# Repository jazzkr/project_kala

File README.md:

View this project on [CADLAB.io](https://cadlab.io/project/22756). 

# project_kala

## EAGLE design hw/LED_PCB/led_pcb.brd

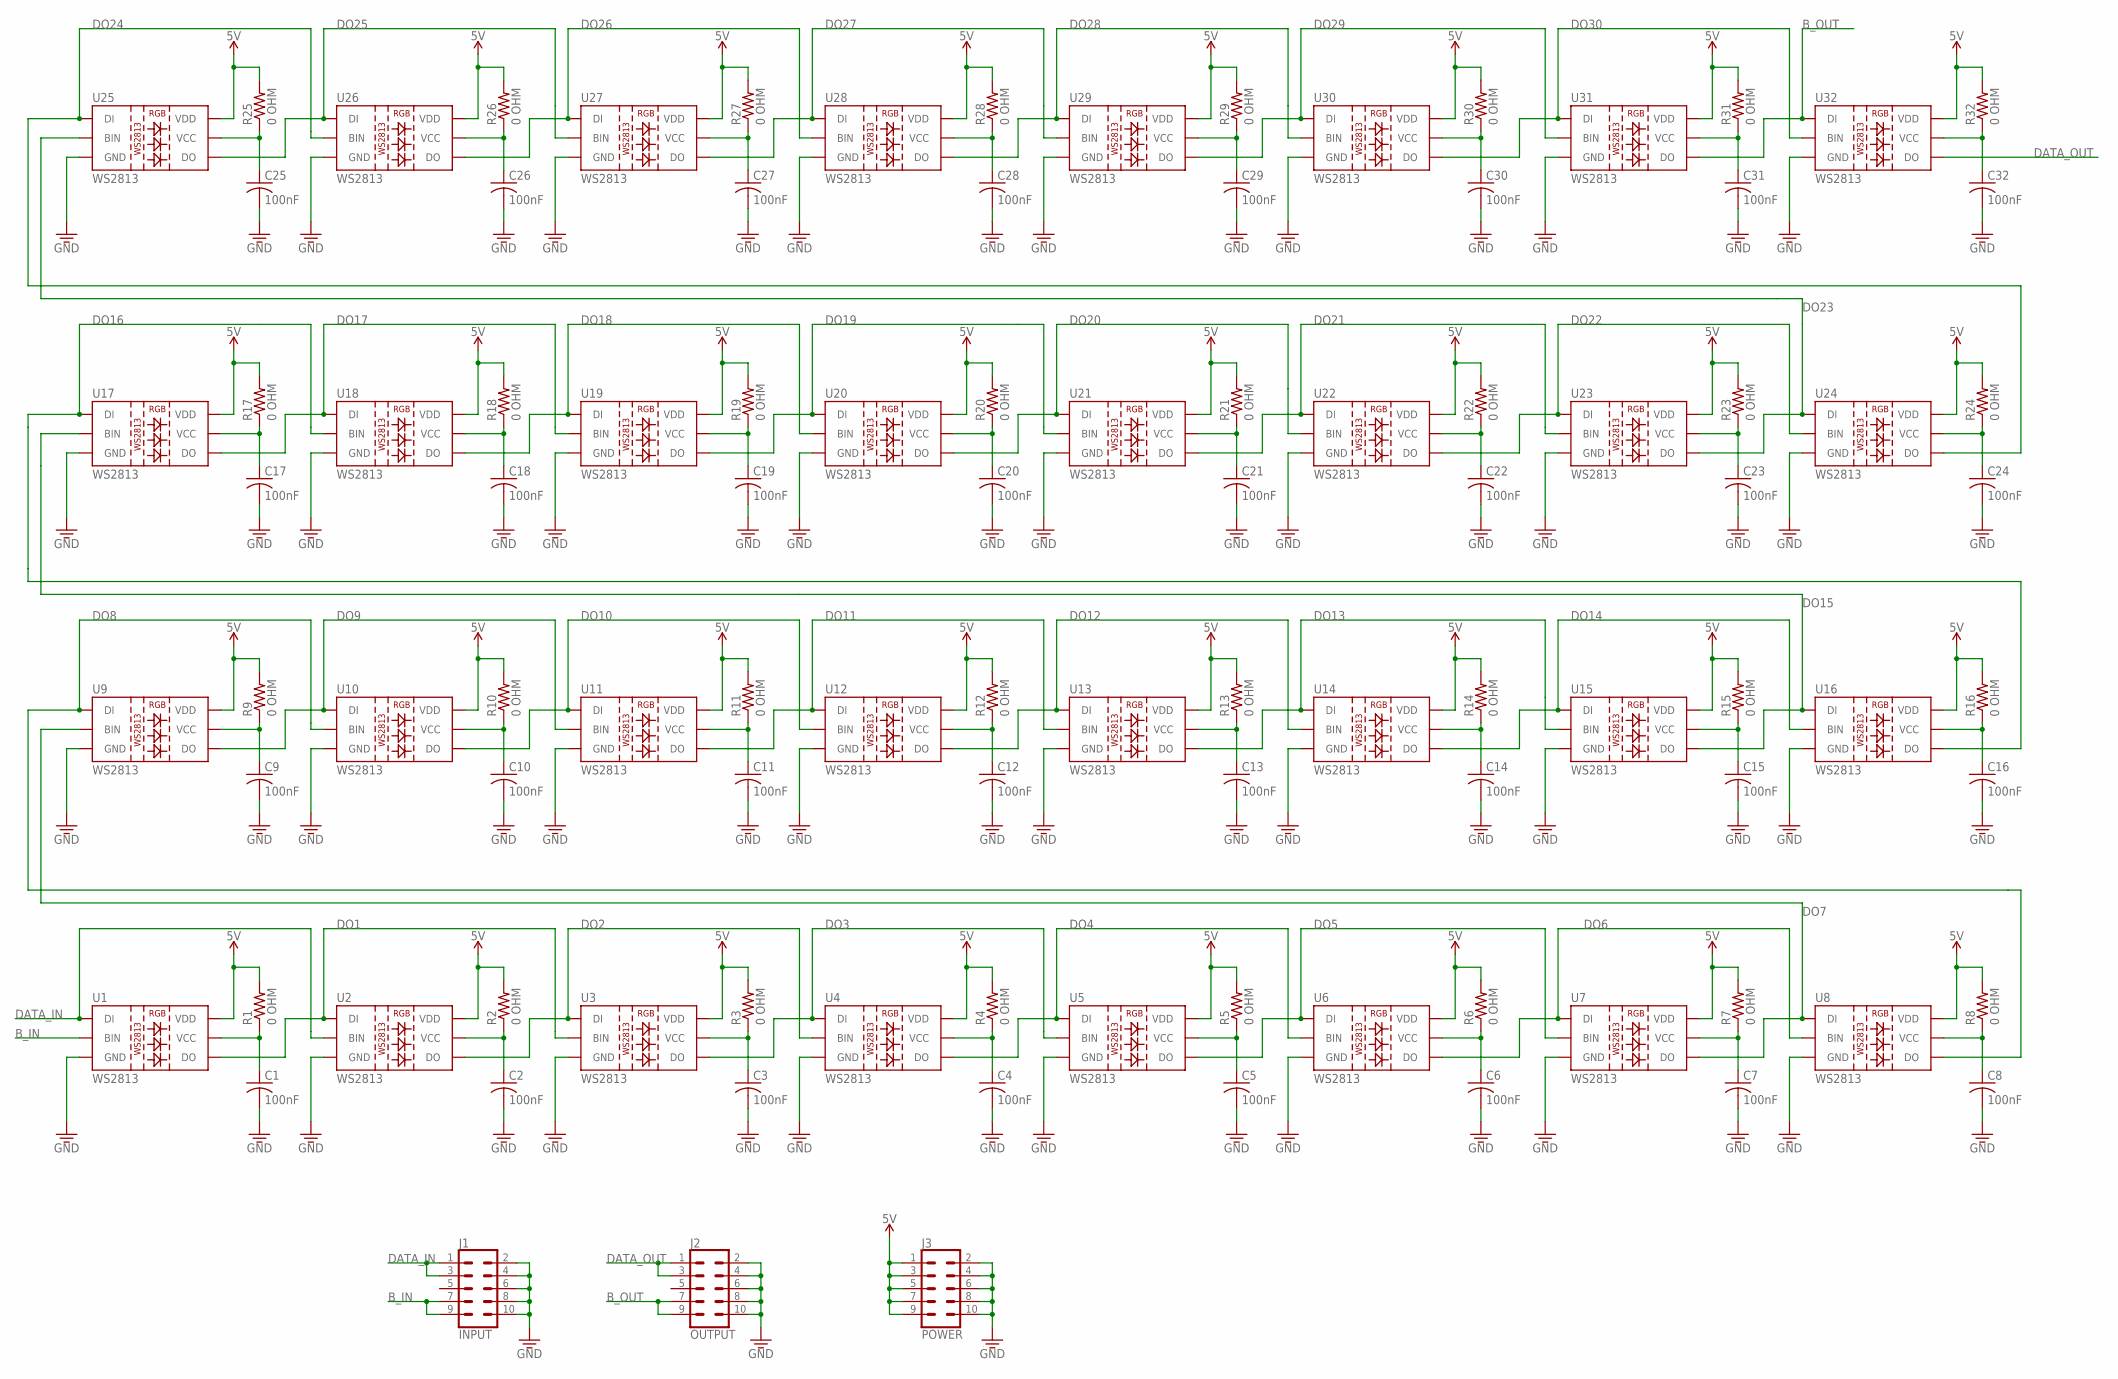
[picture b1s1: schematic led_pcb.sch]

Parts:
C1, C2, C3, C4, C5, C6, C7, C8, C9, C10, C11, C12, C13, C14, C15, C16, C17, C18, C19, C20, C21, C22, C23, C24, C25, C26, C27, C28, C29, C30, C31, C32: 100nF; C0805K
J1: INPUT; 2X5-SHROUDED_SMD
J2: OUTPUT; 2X5-SHROUDED_SMD
J3: POWER; 2X5-SHROUDED_SMD
R1, R2, R3, R4, R5, R6, R7, R8, R9, R10, R11, R12, R13, R14, R15, R16, R17, R18, R19, R20, R21, R22, R23, R24, R25, R26, R27, R28, R29, R30, R31, R32: 0 OHM; M0805
U1, U2, U3, U4, U5, U6, U7, U8, U9, U10, U11, U12, U13, U14, U15, U16, U17, U18, U19, U20, U21, U22, U23, U24, U25, U26, U27, U28, U29, U30, U31, U32: WS2813

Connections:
5V: J3.1, J3.3, J3.5, J3.7, J3.9, R1.2, R2.2, R3.2, R4.2, R5.2, R6.2, R7.2, R8.2, R9.2, R10.2, R11.2, R12.2, R13.2, R14.2, R15.2, R16.2, R17.2, R18.2, R19.2, R20.2, R21.2, R22.2, R23.2, R24.2, R25.2, R26.2, R27.2, R28.2, R29.2, R30.2, R31.2, R32.2, U1.2 (VDD), U2.2 (VDD), U3.2 (VDD), U4.2 (VDD), U5.2 (VDD), U6.2 (VDD), U7.2 (VDD), U8.2 (VDD), U9.2 (VDD), U10.2 (VDD), U11.2 (VDD), U12.2 (VDD), U13.2 (VDD), U14.2 (VDD), U15.2 (VDD), U16.2 (VDD), U17.2 (VDD), U18.2 (VDD), U19.2 (VDD), U20.2 (VDD), U21.2 (VDD), U22.2 (VDD), U23.2 (VDD), U24.2 (VDD), U25.2 (VDD), U26.2 (VDD), U27.2 (VDD), U28.2 (VDD), U29.2 (VDD), U30.2 (VDD), U31.2 (VDD), U32.2 (VDD)
B_IN: J1.7, J1.9, U1.6 (BIN)
B_OUT: J2.7, J2.9, U31.3 (DO), U32.4 (DI)
DATA_IN: J1.1, J1.3, U1.4 (DI), U2.6 (BIN)
DATA_OUT: J2.1, J2.3, U32.3 (DO)
DO1: U1.3 (DO), U2.4 (DI), U3.6 (BIN)
DO2: U2.3 (DO), U3.4 (DI), U4.6 (BIN)
DO3: U3.3 (DO), U4.4 (DI), U5.6 (BIN)
DO4: U4.3 (DO), U5.4 (DI), U6.6 (BIN)
DO5: U5.3 (DO), U6.4 (DI), U7.6 (BIN)
DO6: U6.3 (DO), U7.4 (DI), U8.6 (BIN)
DO7: U7.3 (DO), U8.4 (DI), U9.6 (BIN)
DO8: U8.3 (DO), U9.4 (DI), U10.6 (BIN)
DO9: U9.3 (DO), U10.4 (DI), U11.6 (BIN)
DO10: U10.3 (DO), U11.4 (DI), U12.6 (BIN)
DO11: U11.3 (DO), U12.4 (DI), U13.6 (BIN)
DO12: U12.3 (DO), U13.4 (DI), U14.6 (BIN)
DO13: U13.3 (DO), U14.4 (DI), U15.6 (BIN)
DO14: U14.3 (DO), U15.4 (DI), U16.6 (BIN)
DO15: U15.3 (DO), U16.4 (DI), U17.6 (BIN)
DO16: U16.3 (DO), U17.4 (DI), U18.6 (BIN)
DO17: U17.3 (DO), U18.4 (DI), U19.6 (BIN)
DO18: U18.3 (DO), U19.4 (DI), U20.6 (BIN)
DO19: U19.3 (DO), U20.4 (DI), U21.6 (BIN)
DO20: U20.3 (DO), U21.4 (DI), U22.6 (BIN)
DO21: U21.3 (DO), U22.4 (DI), U23.6 (BIN)
DO22: U22.3 (DO), U23.4 (DI), U24.6 (BIN)
DO23: U23.3 (DO), U24.4 (DI), U25.6 (BIN)
DO24: U24.3 (DO), U25.4 (DI), U26.6 (BIN)
DO25: U25.3 (DO), U26.4 (DI), U27.6 (BIN)
DO26: U26.3 (DO), U27.4 (DI), U28.6 (BIN)
DO27: U27.3 (DO), U28.4 (DI), U29.6 (BIN)
DO28: U28.3 (DO), U29.4 (DI), U30.6 (BIN)
DO29: U29.3 (DO), U30.4 (DI), U31.6 (BIN)
DO30: U30.3 (DO), U31.4 (DI), U32.6 (BIN)
GND: C1.2, C2.2, C3.2, C4.2, C5.2, C6.2, C7.2, C8.2, C9.2, C10.2, C11.2, C12.2, C13.2, C14.2, C15.2, C16.2, C17.2, C18.2, C19.2, C20.2, C21.2, C22.2, C23.2, C24.2, C25.2, C26.2, C27.2, C28.2, C29.2, C30.2, C31.2, C32.2, J1.2, J1.4, J1.6, J1.8, J1.10, J2.2, J2.4, J2.6, J2.8, J2.10, J3.2, J3.4, J3.6, J3.8, J3.10, U1.5 (GND), U2.5 (GND), U3.5 (GND), U4.5 (GND), U5.5 (GND), U6.5 (GND), U7.5 (GND), U8.5 (GND), U9.5 (GND), U10.5 (GND), U11.5 (GND), U12.5 (GND), U13.5 (GND), U14.5 (GND), U15.5 (GND), U16.5 (GND), U17.5 (GND), U18.5 (GND), U19.5 (GND), U20.5 (GND), U21.5 (GND), U22.5 (GND), U23.5 (GND), U24.5 (GND), U25.5 (GND), U26.5 (GND), U27.5 (GND), U28.5 (GND), U29.5 (GND), U30.5 (GND), U31.5 (GND), U32.5 (GND)
unnamed: C1.1, R1.1, U1.1 (VCC)
unnamed: C2.1, R2.1, U2.1 (VCC)
unnamed: C3.1, R3.1, U3.1 (VCC)
unnamed: C4.1, R4.1, U4.1 (VCC)
unnamed: C5.1, R5.1, U5.1 (VCC)
unnamed: C6.1, R6.1, U6.1 (VCC)
unnamed: C7.1, R7.1, U7.1 (VCC)
unnamed: C8.1, R8.1, U8.1 (VCC)
unnamed: C17.1, R17.1, U17.1 (VCC)
unnamed: C18.1, R18.1, U18.1 (VCC)
unnamed: C19.1, R19.1, U19.1 (VCC)
unnamed: C9.1, R9.1, U9.1 (VCC)
unnamed: C10.1, R10.1, U10.1 (VCC)
unnamed: C11.1, R11.1, U11.1 (VCC)
unnamed: C12.1, R12.1, U12.1 (VCC)
unnamed: C13.1, R13.1, U13.1 (VCC)
unnamed: C14.1, R14.1, U14.1 (VCC)
unnamed: C15.1, R15.1, U15.1 (VCC)
unnamed: C16.1, R16.1, U16.1 (VCC)
unnamed: C20.1, R20.1, U20.1 (VCC)
unnamed: C21.1, R21.1, U21.1 (VCC)
unnamed: C22.1, R22.1, U22.1 (VCC)
unnamed: C23.1, R23.1, U23.1 (VCC)
unnamed: C24.1, R24.1, U24.1 (VCC)
unnamed: C25.1, R25.1, U25.1 (VCC)
unnamed: C26.1, R26.1, U26.1 (VCC)
unnamed: C27.1, R27.1, U27.1 (VCC)
unnamed: C28.1, R28.1, U28.1 (VCC)
unnamed: C29.1, R29.1, U29.1 (VCC)
unnamed: C30.1, R30.1, U30.1 (VCC)
unnamed: C31.1, R31.1, U31.1 (VCC)
unnamed: C32.1, R32.1, U32.1 (VCC)

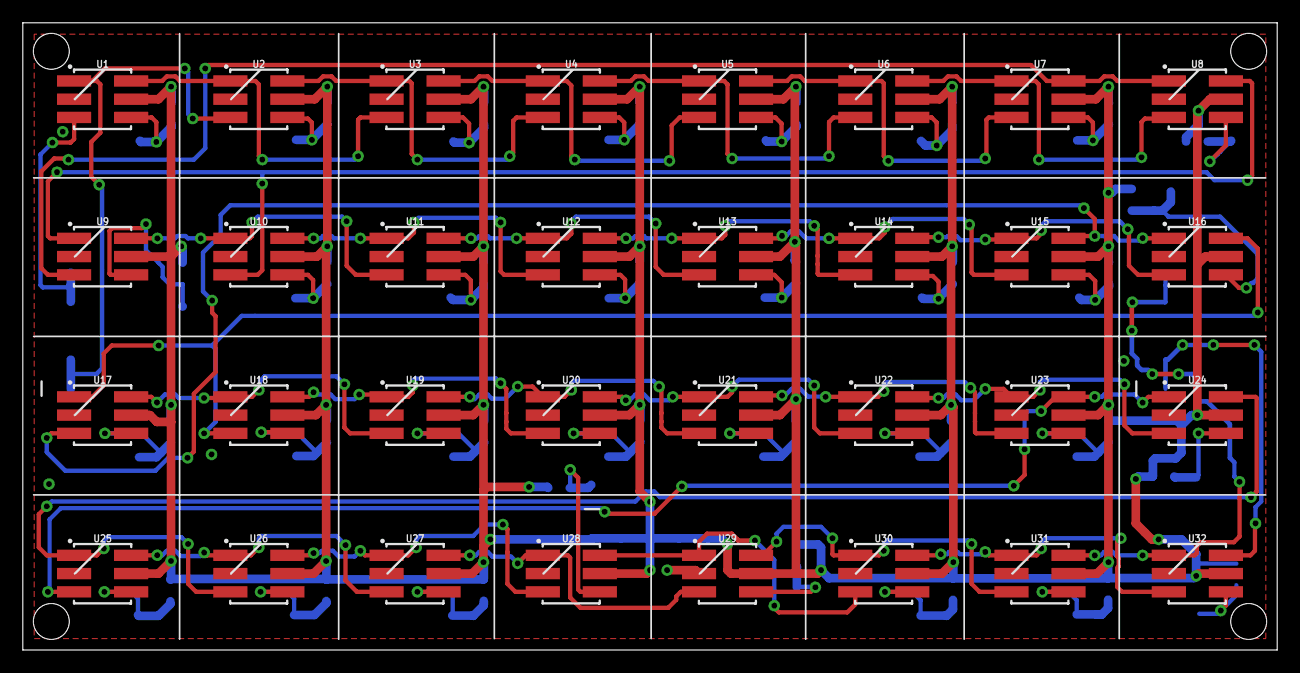
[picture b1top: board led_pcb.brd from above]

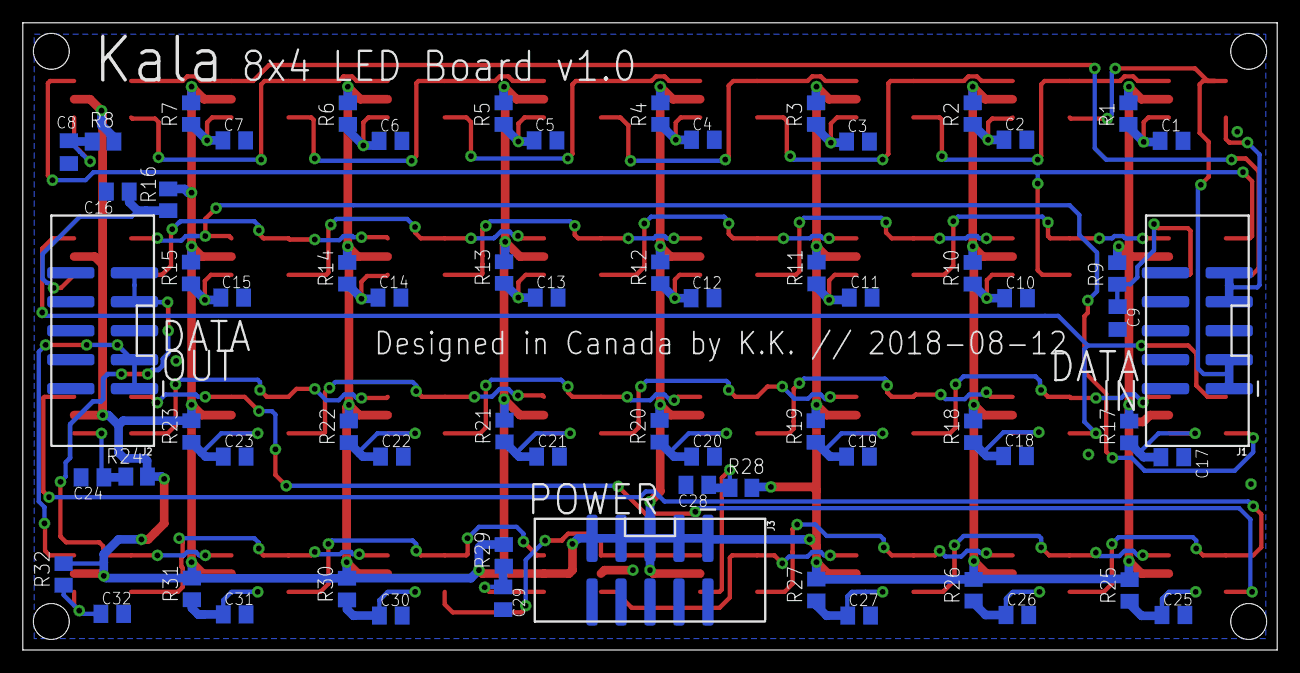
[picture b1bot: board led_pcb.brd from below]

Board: 2 copper layers, 110.0 x 55.0 mm, 99 parts (67 on the bottom side), 68 nets.

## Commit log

2018-08-15 Committing progress up until now
2018-08-15 Final touches on LED pcb
2019-01-13 Re-org to use kicad for hat PCB
2019-01-13 Add schematic symbols for most components
2019-01-14 Schematic mostly done, started prelim layout
2019-01-17 Added RTC, changed layout a bit
2019-01-18 Added pull ups, LEDs, & swapped out cap touch IC
2019-01-23 change back RTC, finish placement mostly
2019-12-28 Commit WIP on new main LED PCB
2020-01-25 Add all files, sort out later
2020-02-06 Add gitignore for kicad, mac OS, python, C, C++:
2020-02-06 Add WiP pixel planner
2020-02-06 Fix grid system
2020-02-07 Add pixel color change capability
2020-02-07 Start to flesh out pixel frames & animations
2020-02-07 Small fix
2020-02-15 More work on pixel planner
2020-02-22 Save progress
2020-04-02 WiP, rearrange interface + add playback
2020-04-03 Changes to mechanical, PCBs, + pixel planner SW
2020-04-03 Update gitignore
2020-04-03 More gitignore tweaks
2020-04-05 Backlink to CADLAB.io has been added.

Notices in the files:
parts and their libraries:
SparkFun-Connectors: Licensing: Creative Commons ShareAlike 4.0 International - https://creativecommons.org/licenses/by-sa/4.0
